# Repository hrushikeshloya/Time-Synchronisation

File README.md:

# EDL-TimeSync
Public Repository of our Electronic Design Lab Project Time Synchronization in Vibration Sensors under Prof. M.C. Chandorkar

Members:
1. Hrushikesh Loya (150010017@iitb.ac.in)
2. Rajat Patel (150010002@iitb.ac.in)
3. Yashswi Jain (150110039@iitb.ac.in)

### About

The project attempts to build a customizable skeleton which can be used to synchronise multiple sensors to take time stamped readings and transmit it to the user. 

We have developed a skeleton that can accommodate two vibration sensors (MMA7361, in our case) mounted on two self-designed and realised peripheral microcontrollers with ATMEGA-328P and a customised central Microprocessor for collecting the sampled and stamped data from both of them and sending them them to the UNIX PC for further analysis. 

### Board Design

You can find the eagle schematic and board files for both the central and peripheral microcontroller in Board Design folder.

### Communication Protocols

#### Mode 1 (CSS)
Continuous Sampling and Sending: The sampled data is sent to PC by each of the two Local Microprocessors alternatively. The sampling is done through interrupts and time spent in each interrupt service routine as mentioned above is 35 microseconds. This doesn’t affect the transmission as ATMEGA328p has 64 byte buffer for Serial transmission.
Maximum Attainable sampling rate: 2.5KHz

#### Mode 2 (Burst Mode)
Sampling till buffer is full and then sending in a burst: In this method we sample the data till the buffer is full and then send the data from 2 Local Microprocessors to the PC alternatively. The sampling of Data is stopped when the data is transmitted to PC. The sampling starts only after both the Local Microprocessors are done with the transmission.
Maximum Attainable sampling rate: 25KHz

### Time Synchronization

As the two peripheral microcontrollers have different clocks, there will be drifts in both the clocks after some time. To match the sampling instants, we use the same square wave which we sent from central for alternate data sending.

If there is drift in clocks, the timer1 (inbuilt timer in Atmega328P) values will not be same. So after certain number of cycles of square wave we set the the timer1 values of both the  microprocessors to initial values. And we send the timestamp when the synchronization is done to PC from Central Microprocessor. This way we acheive synchronized data.

### Firmware

##### How to upload the code?
Use Arduino IDE, to compile and upload the code. central.ino corresponds to central microprocessor, interrupt_transmit.ino corresponds to first peripheral, and interrupt_transmit2.ino corresponds to second peripheral.

##### Aquiring Serial Data on PC?
We use picocom (sudo apt-get install picocom) to aquire the serial data on ubuntu based PC. 
sudo picocom -b 230400 /dev/ttyUSB0 | tee logfile  (check your port on which arduino is connected, our case it was /dev/ttyUSB0)  saves the data from the serial port of the computer to a log file named logfile.

##### Plotting and Interpretting the data?
The data we recieve is in byte format.
You can then use log_reader_v1.py and log_reader_v2.py to plot the data aquired without time sync and with timesync respectively.

### Results

You can have a view of few of the amazing results (with their log files) we have obtained in the Results folder

Link to our complete report: https://docs.google.com/document/d/1JRsnFTGfe37P0LFT0vE4qM5fWR5oT6ynj_dwdIWIZMQ/edit?usp=sharing

Link to the final presenentation: https://docs.google.com/presentation/d/1-vB_suMupCKIn_ZJjNBb9ri4n2t6BEERArDRMrE7F0k/edit?usp=sharing

Refrences: 

1. "Time synchronization of a wired sensor network for structural health monitoring":  http://iopscience.iop.org/article/10.1088/0964-1726/17/01/015016

Chalte Hai!

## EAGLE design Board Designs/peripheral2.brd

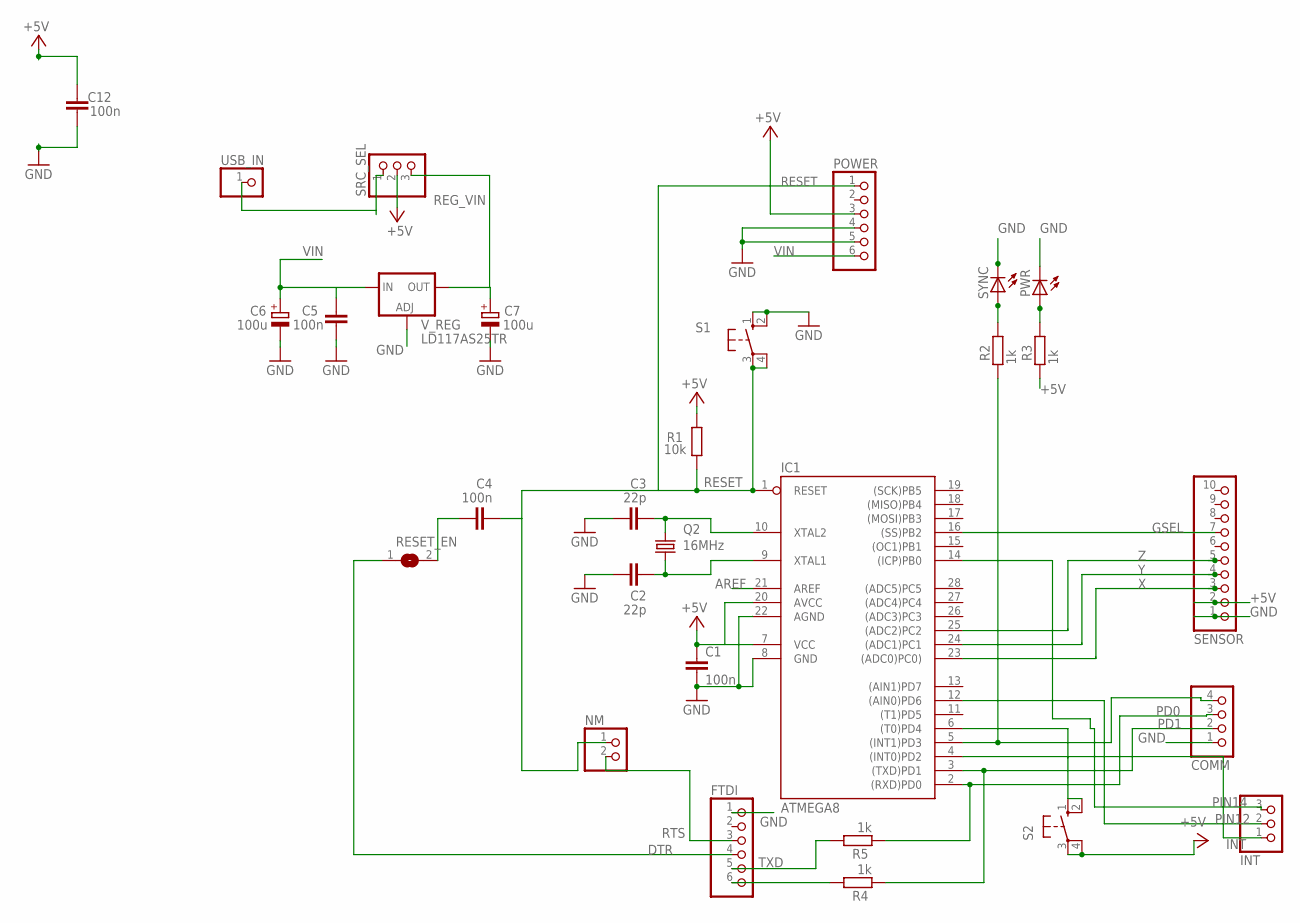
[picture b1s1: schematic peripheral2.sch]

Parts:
C1, C4, C5, C12: 100n; C1206
C2, C3: 22p; C1206
C6, C7: 100u; PANASONIC_D
COMM: PINHD-1X4; 1X04
FTDI: PINHD-1X6; 1X06
IC1: ATMEGA8; DIL28-3
INT: PINHD-1X3; 1X03
NM: PINHD-1X2; 1X02
POWER: PINHD-1X6; 1X06
PWR: LEDCHIPLED_1206; CHIPLED_1206
Q2: 16MHz; HC49/S
R1: 10k; R1206
R2, R3, R4, R5: 1k; R1206
RESET_EN: SJ
S1, S2: 10-XX; B3F-10XX
SENSOR: PINHD-1X10; 1X10
SRC_SEL: PINHD-1X3; 1X03
SYNC: LEDCHIPLED_1206; CHIPLED_1206
USB_IN: PINHD-1X1; 1X01
V_REG: LD117AS25TR; SOT223

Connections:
+5V: C1.1, C12.2, IC1.7 (VCC), IC1.20 (AVCC), POWER.3, R1.2, R3.2, S2.3, S2.4 (P1), SENSOR.2, SRC_SEL.2
A3: COMM.4, IC1.5 ((INT1)PD3), R2.2
AREF: IC1.21 (AREF)
DTR: FTDI.4, RESET_EN.1
GND: C1.2, C2.1, C3.1, C5.1, C6.-, C7.-, C12.1, COMM.1, FTDI.1, IC1.8 (GND), IC1.22 (AGND), POWER.4, POWER.5, PWR.C, S1.1 (S), S1.2 (S1), SENSOR.1, SYNC.C, V_REG.1 (ADJ)
GSEL: IC1.16 ((SS)PB2), SENSOR.7
INT: IC1.4 ((INT0)PD2), INT.1
unnamed: R2.1, SYNC.A
unnamed: PWR.A, R3.1
unnamed: FTDI.6, R4.1
unnamed: C2.2, IC1.9 (XTAL1), Q2.1
unnamed: C3.2, IC1.10 (XTAL2), Q2.2
unnamed: IC1.6 ((T0)PD4), S2.1 (S), S2.2 (S1)
unnamed: C4.1, RESET_EN.2
PD0: COMM.3, IC1.2 ((RXD)PD0), R5.2
PD1: COMM.2, IC1.3 ((TXD)PD1), R4.2
PIN12: IC1.12 ((AIN0)PD6), INT.2
PIN14: IC1.14 ((ICP)PB0), INT.3
REG_VIN: C7.+, SRC_SEL.3, V_REG.4 (OUT)
RESET: C4.2, IC1.1 (RESET), NM.1, POWER.1, R1.1, S1.3, S1.4 (P1)
RTS: FTDI.3, NM.2
TXD: FTDI.5, R5.1
USB_VCC: SRC_SEL.1, USB_IN.1
VIN: C5.2, C6.+, POWER.6, V_REG.3 (IN)
X: IC1.23 ((ADC0)PC0)), SENSOR.3
Y: IC1.24 ((ADC1)PC1), SENSOR.4
Z: IC1.25 ((ADC2)PC2), SENSOR.5

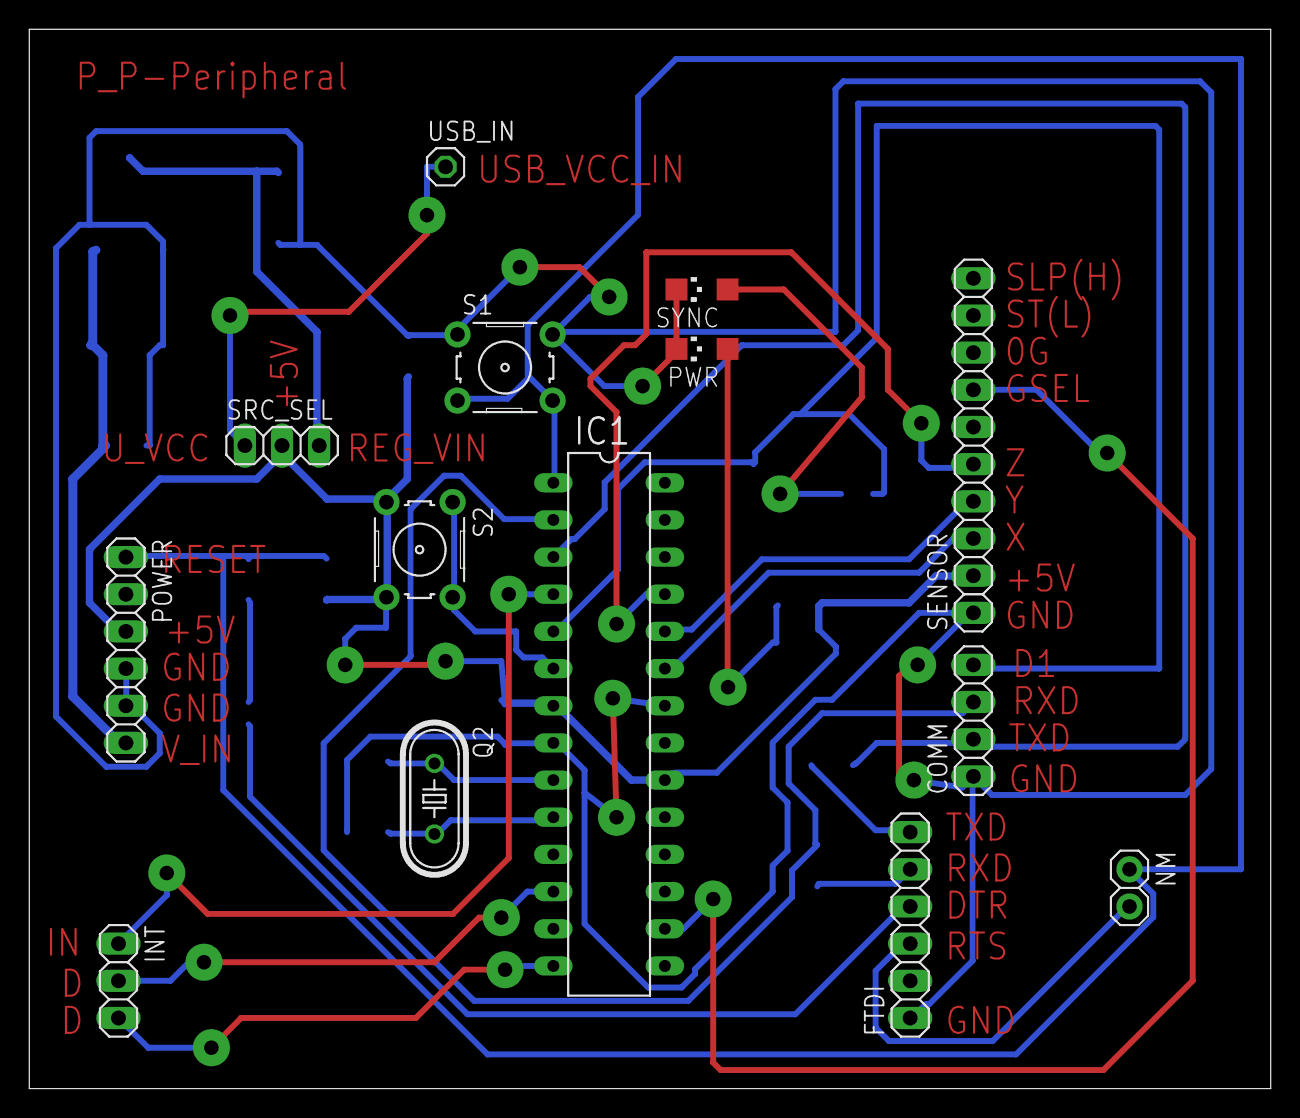
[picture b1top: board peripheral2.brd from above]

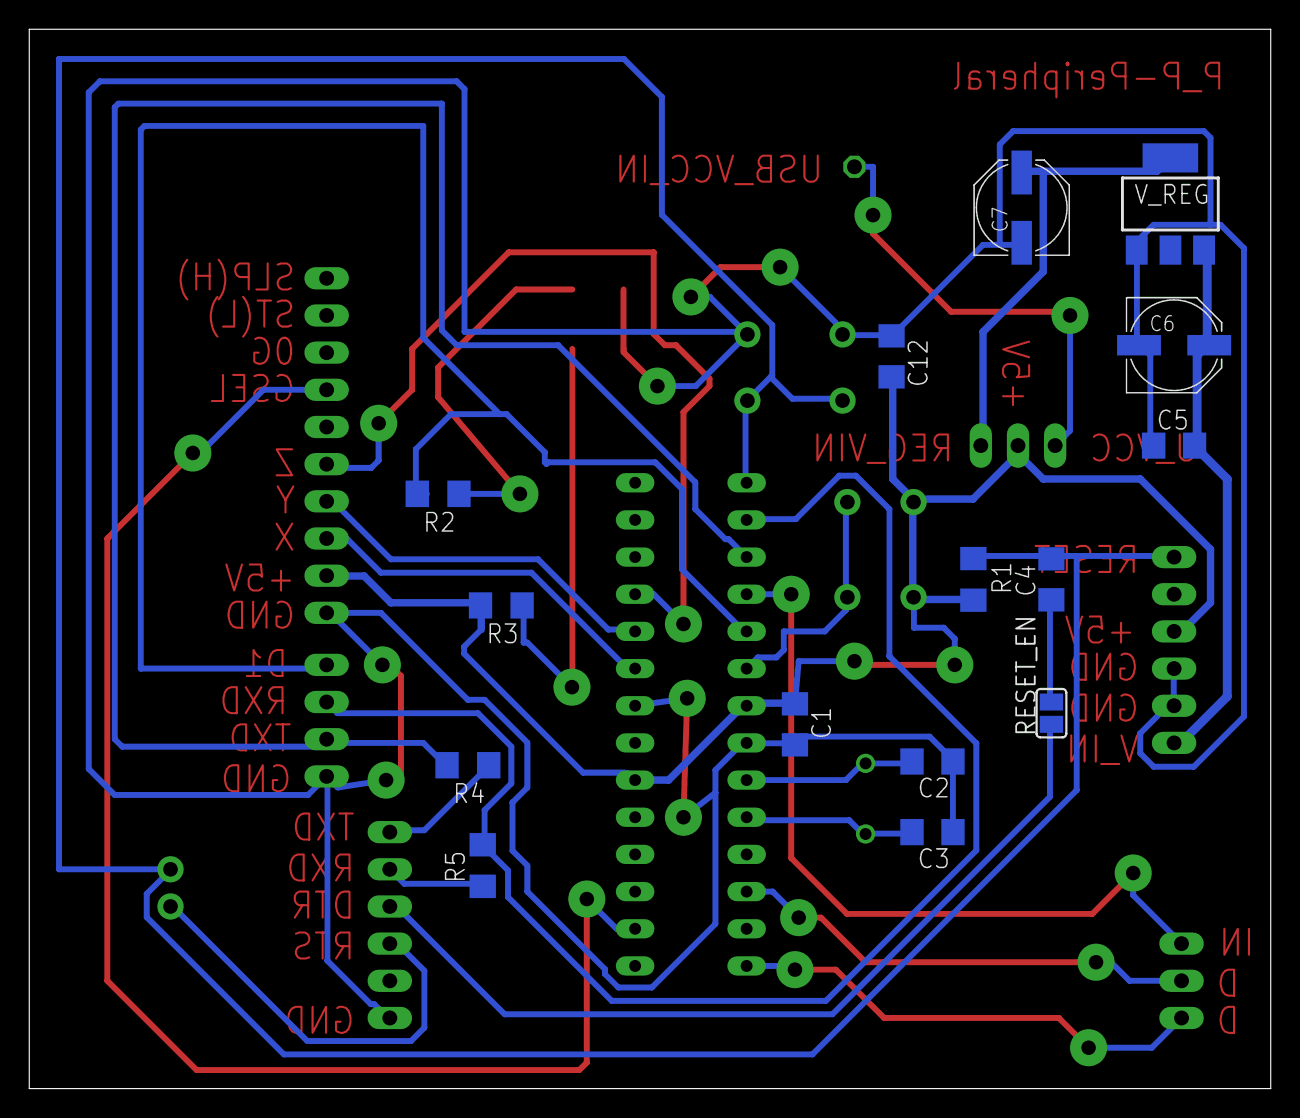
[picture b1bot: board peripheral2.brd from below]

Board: 2 copper layers, 84.8 x 72.4 mm, 29 parts (15 on the bottom side), 26 nets.

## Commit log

2018-04-29 Updating Readme.md
2018-04-30 Adding the source code and board designs
2018-04-30 updating readme
2018-04-30 Adding important results
2018-04-30 Updating unix interface python files
2018-04-30 Added Results
2018-04-30 see the changes
2018-04-30 dekh le
2018-04-30 dekh le 2
2018-04-30 dekh le 3
